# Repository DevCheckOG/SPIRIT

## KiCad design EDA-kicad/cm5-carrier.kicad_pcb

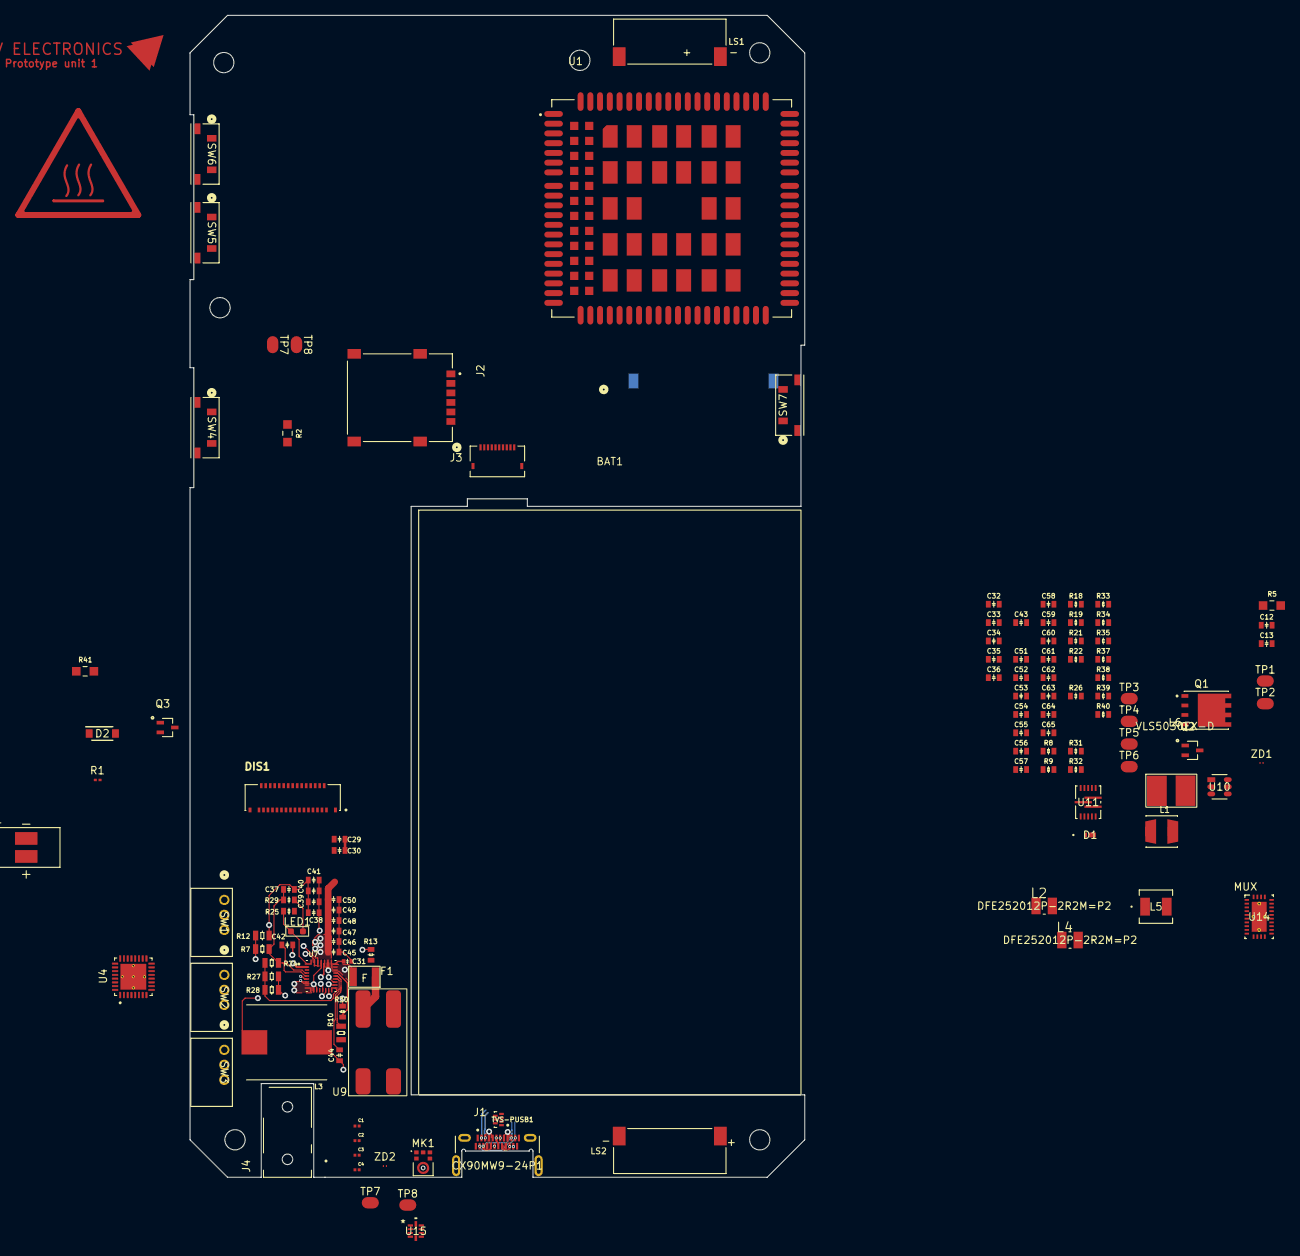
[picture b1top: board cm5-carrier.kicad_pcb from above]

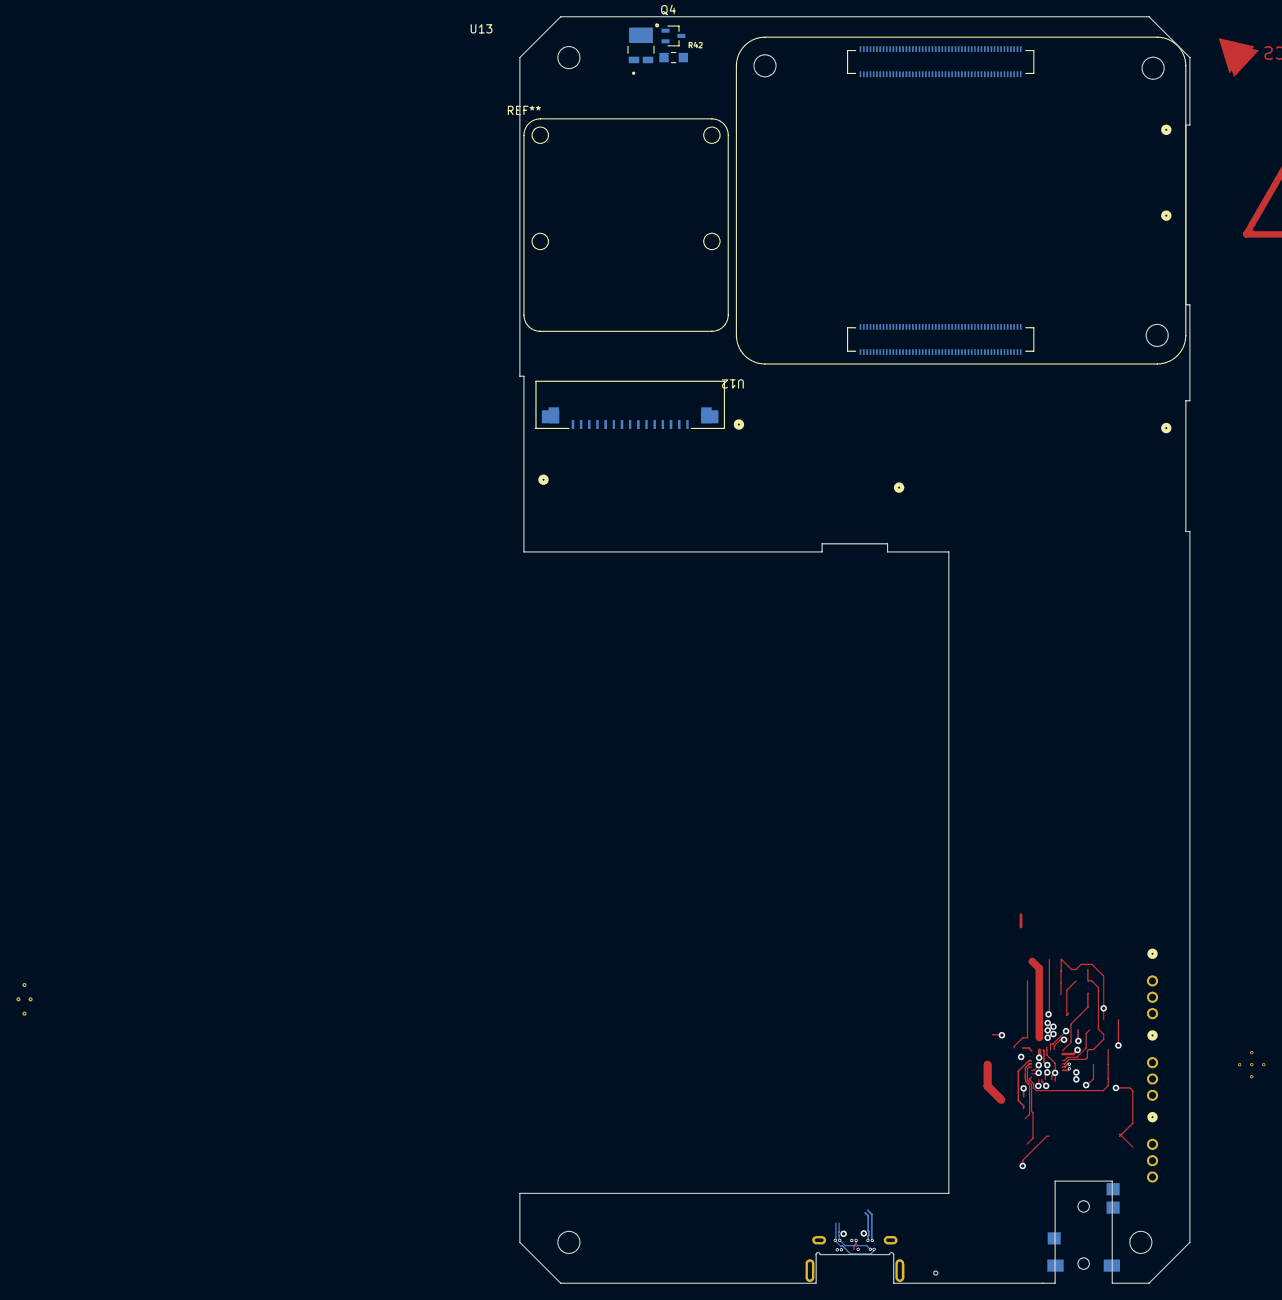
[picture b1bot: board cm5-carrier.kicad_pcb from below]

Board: 6 copper layers, 82.0 x 155.0 mm, 129 parts (5 on the bottom side), 101 nets.

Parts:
B1: VIBR; VIBRATION-PUI_HD-EMB1205-3-SC-R
BAT1: Li-ion-3.7 35Ah; battery_37V3500mAhLP685077JU
C1, C2, C3, C4: 0.33 µF coupling cap; USBC_capacitor_CAPC0603X33N
C12: 200pF; 0603-capacitor
C13, C38, C45, C55, C59: 0.1uF; 0603-capacitor
C29, C30, C33, C34, C35, C39, C40, C41, C46, C47, C48, C49, C50: 10uF; 0603-capacitor
C31: 1nF 50V; 0402-capacitor
C32, C53, C54: 1uF; 0603-capacitor
C36, C43, C51, C56, C57, C58, C60, C61, C62, C65: 22uF; 0603-capacitor
C37, C52, C64: 4.7uF; 0603-capacitor
C42, C44: 47nF; 0603-capacitor
C63: 6.8nF; 0603-capacitor
D1: D_Schottky; schottky-diode-CR_DSN2_152AB-C_OSI
D2: 1N4007W-T; flyback-diode-SODFL3818X130N
DIS1: FH72-31S-0.3SHW; HRS_FH72-31S-0.3SHW
F1: 9A 6V; PTC RESET FUSE 9.0A 6V 1210 1210L900SLPR
J1: USBC-4-0-CX90MW9-24P1; USB-4-0-HIROSE_CX90MW9-24P1
J2: SIM-G85D1160022HHR; SIM-AMPHENOL_G85D1160022HHR
J3: FINGER; 10PIN
J4: SJ2-35894B-SMT-TR; 35mmJACK-CUI_SJ2-35894B-SMT-TR
L1: 3.3uH; 3-3uH-MURATA_LQH44PN3R3MPRL
L2, L4: 2.2uH; 2-2uH-inductor-INDC2520X120N
L3: 2.2uH; 2-2uh-inductorIND_ETQP4M2R2KVC
L5: 6.8uH; 6-8uH-inductor-LQH44PN6R8MPRLIND_LQH44PN_PR_MUR
L6: 1.5uH; 1-5uH-inductor-VLS5030EX-D
LED1: 5mA 2V Fv; LED-INDICATOR-RED-QBLP601-R5
LS1, LS2: CMR-15062S-67; SPEAKER_CMR-15062S-67
MK1: microphone; microphone_SPH0645LM4H-B
Module1: ComputeModule5-CM5; Raspberry-Pi-5-Compute-Module
Q1: NMOS-BSC0902NSIATMA1-PG-TDSON-8-6-IC_ISC037N03L5ISATMA1
Q2, Q3, Q4: gpio-driver-transistor-fix-SOT65P210X110-3N
R1: thermistor; thermistor-NTC0201Z_P63XP33_PAN
R2: 270KΩ 0.5W; 1K-05W-0805-RES_ERJP06J102V
R5: 100KΩ; 100K-0805-resistor-RES_ERA6AEB104V
R7: 127kΩ; 0805-resistor
R8, R9: 10k; 0603-resistor
R10: 4.7KΩ; 0805-resistor
R12: 100kΩ; 0805-resistor
R13: 100Ω; 0603-resistor
R18, R31, R32, R33: 100kΩ; 0603-resistor
R19: 680kΩ 1%; 0603-resistor
R21, R26: 470kΩ 1%; 0603-resistor
R22: 1MΩ 1%; 0603-resistor
R24: 5.23kΩ; 0805-resistor
R25, R30: 10kΩ; 0603-resistor
R27: 10kΩ; 0805-resistor
R28: 30kΩ; 0805-resistor
R29: 680Ω; 0603-resistor
R34: 820kΩ; 0603-resistor
R35: 182KΩ; 0603-resistor
R37: 5Ω; 0603-resistor
R38: 750kΩ; 0603-resistor
R39: 200kΩ; 0603-resistor
R40: 6.8kΩ; 0603-resistor
R41, R42: 1KΩ 0.5W; 1K-05W-0805-RES_ERJP06J102V
SW1: EG25-switch-CSS-1210MC; privacy-switch-SW3_CSS-1210MC_NDC
SW2: MIC-switch-CSS-1210MC; privacy-switch-SW3_CSS-1210MC_NDC
SW3: CAM-switch-CSS-1210MC; privacy-switch-SW3_CSS-1210MC_NDC
SW4: PROG; buttonSW_TL3330_EWI
SW5: VOL-; buttonSW_TL3330_EWI
SW6: VOL+; buttonSW_TL3330_EWI
SW7: POW; buttonSW_TL3330_EWI
TP1, TP2, TP3, TP4, TP5, TP6, TP7, TP7#2, TP8, TP8#2: test-pad-1
TVS-PUSB1: TVS-array-IC_PUSB3AB6Z
U1: EG25GGC-128-SGNS; XCVR_EG25GGC-128-SGNS
U4: CODEC-TLV320AIC3204IRHBR; CODEC-QFN50P500X500X100-33N
U7: BQ25792RQMR; charger-bq25792-QFN40P400X400X100-29N
U9: BAT-CONNECTOR-FLTS22WR00
U10: 22V-boost-AP3032KTR-G1; SOT23-6_DIO
U11: MP3429GL-Z; QFN-3x4_MP3429_MNP
U12: FPC15pin-1mm-pitch-F52Q-1A7H1-11015; FPC15pin-1mm-pitch-CONN_F52Q-1A7H1-11015_AMP
U13: Flash-LED-Lumiled; LUMILED-DIODFN449X305X210-3N
U14: HD3SS460RHRR; USB-MUX-RHR0028A
U15: USB SWITCH 2CHANNEL TS3USB221AQRSERQ1; USB-SWITCH-2CHANNEL-TS3USB221AQRSERQ1
ZD1, ZD2: protection-PESD5V0C1USFYL; USB-ESD-protection-diode-PESD5V0C1USFYL-SOD962-2_DSN0603-2_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

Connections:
1V8: DIS1.25, SW2.1, U4.24 (AVDD), U4.29 (DVDD)
3V3B: DIS1.30, Module1.78 (GPIO_VREF(1.8v/3.3v_Input)), Q2.3 (S), R8.2, R9.1, R25.2, R30.1, R31.1, R32.1, R33.2, SW3.1, U4.6 (IOVDD), U4.26 (LDOIN/HPVDD), U4.30 (LDO_SELECT)
5V: C59.1, C60.1, C61.1, C62.1, Module1.77 (+5v_(Input)), Module1.79 (+5v_(Input)), Module1.81 (+5v_(Input)), Module1.83 (+5v_(Input)), Module1.85 (+5v_(Input)), Module1.87 (+5v_(Input)), R38.1, U11.8 (VOUT)
22V: C53.1, D1.1 (K), DIS1.2, U10.5 (OV)
AGND: C65.2, R39.2, R40.2, U11.6 (AGND), U11.9 (FTY)
AUDIO_BCLK_I2S: MK1.4 (BCLK), Module1.49 (GPIO18), U4.2 (BCLK)
AUDIO_MCLK: Module1.54 (GPIO4), U4.1 (MCLK)
AUDIO_MIC_DATA: Module1.27 (GPIO20), U4.5 (DOUT/MFP2)
AUDIO_RESET: Module1.45 (GPIO24), U4.31 (~RESET)
AUDIO_SCL: Module1.51 (GPIO15), U4.9 (SCL/~SS)
AUDIO_SDA: Module1.31 (GPIO12), U4.10 (SDA/MOSI)
AUDIO_SOUND_DATA: Module1.25 (GPIO21), U4.4 (DIN/MFP1)
AUDIO_WCLK_I2S: MK1.1 (WS), Module1.26 (GPIO19), U4.3 (WCLK)
BACKLIGHT-: DIS1.31, R37.1, U10.3 (FB)
BAT+: C29.1, C30.1, F1.2, R13.2, U7.22 (BAT), U7.23 (BAT__1)
CAM-SWITCH: TP7.1 (A), U12.15
CAM_CK_N: Module1.127 (MIPI0_C_N), U12.8
CAM_CK_P: Module1.129 (MIPI0_C_P), U12.9
CAM_D0_N: Module1.115 (MIPI0_D0_N), U12.2
CAM_D0_P: Module1.117 (MIPI0_D0_P), U12.3
CAM_D1_N: Module1.121 (MIPI0_D1_N), U12.5
CAM_D1_P: Module1.123 (MIPI0_D1_P), U12.6
CAM_IO0: TP8.1 (A), U12.11
CC1: J1.A5 (CC1), Module1.94 (CC1)
CC2: J1.B5 (CC2), Module1.96 (CC2)
D+: J1.A6 (D1+), J1.B6 (D2+), Module1.163 (USB3-1-D_P), TVS-PUSB1.5 (D+), U7.6 (D+)
D-: J1.A7 (D1-), J1.B7 (D2-), Module1.165 (USB3-1-D_N), TVS-PUSB1.4 (D-), U7.7 (D-)
DEFDCDC1 DIVIDER: C36.1, L1.1, R34.1
DSI1_C_N: DIS1.11, Module1.187 (MIPI1_C_N)
DSI1_C_P: DIS1.12, Module1.189 (MIPI1_C_P)
DSI1_D0_N: DIS1.5, Module1.175 (MIPI1_D0_N)
DSI1_D0_P: DIS1.6, Module1.177 (MIPI1_D0_P)
DSI1_D1_N: DIS1.8, Module1.181 (MIPI1_D1_N)
DSI1_D1_P: DIS1.9, Module1.183 (MIPI1_D1_P)
DSI1_D2_N: DIS1.14, Module1.133 (MIPI0_D2_N), Module1.193 (MIPI1_D2_N)
DSI1_D2_P: DIS1.15, Module1.135 (MIPI0_D2_P), Module1.195 (MIPI1_D2_P)
GND: C12.1, C13.2, C29.2, C30.2, C31.2, C32.2, C33.2, C34.2, C35.2, C36.2, C37.2, C38.2, C39.2, C40.2, C41.2, C43.2, C45.2, C46.2, C47.2, C48.2, C49.2, C50.2, C51.2, C52.1, C53.2, C54.2, C56.2, C57.2, C58.2, C59.2, C60.2, C61.2, C62.2, C64.1, DIS1.1, DIS1.4, DIS1.7, DIS1.10, DIS1.13, DIS1.16, DIS1.19, DIS1.20, J1.A1 (GND_A), J1.A12 (GND_A__1), J1.B1 (GND_B), J1.B12 (GND_B__1), J1.SH1 (SHIELD), J1.SH2 (SHIELD__1), J1.SH3 (SHIELD__2), J1.SH4 (SHIELD__3), J2.C5 (GND), J2.S1 (SHIELD_GND), J2.S2 (SHIELD_GND__1), J2.S3 (SHIELD_GND__2), J3.1, J4.1, MK1.2 (SELECT), MK1.3 (GND), Module1.1 (GND), Module1.2 (GND), Module1.8 (GND), Module1.13 (GND), Module1.14 (GND), Module1.22 (GND), Module1.23 (GND), Module1.32 (GND), Module1.33 (GND), Module1.42 (GND), Module1.43 (GND), Module1.52 (GND), Module1.53 (GND), Module1.60 (GND), Module1.66 (GND), Module1.71 (GND), Module1.74 (GND), Module1.98 (GND), Module1.107 (GND), Module1.108 (GND), Module1.113 (GND), Module1.114 (GND), Module1.119 (GND), Module1.120 (GND), Module1.125 (GND), Module1.126 (GND), Module1.131 (GND), Module1.132 (GND), Module1.137 (GND), Module1.138 (GND), Module1.144 (GND), Module1.150 (GND), Module1.155 (GND), Module1.156 (GND), Module1.161 (GND), Module1.162 (GND), Module1.167 (GND), Module1.168 (GND), Module1.173 (GND), Module1.174 (GND), Module1.179 (GND), Module1.180 (GND), Module1.185 (GND), Module1.186 (GND), Module1.191 (GND), Module1.192 (GND), Module1.197 (GND), Module1.198 (GND), Q3.3 (S), Q4.3 (S), R5.1, R10.1, R12.2, R21.1, R26.1, R27.2, R28.2, R35.1, R37.2, TVS-PUSB1.2 (GND), U4.7 (IOVSS), U4.12 (SPI_SELECT), U4.17 (AVSS), U4.28 (DVSS), U4.33 (EP), U7.10 (ACDRV2), U7.11 (ACDRV1), U7.27 (GND), U9.4 (OUT-), U10.2 (GND), U11.7 (PGND), U12.1, U12.4, U12.10, ZD1.2, ZD2.2
GPIO2: Module1.58 (GPIO2), SW7.2
GPIO3: Module1.56 (GPIO3), SW6.2
GPIO17: Module1.50 (GPIO17), SW4.2
GPIO22: Module1.46 (GPIO22), R42.1
GPIO27: Module1.48 (GPIO27), R41.1
JACK_MIC: J4.4, U4.8 (SCLK/MFP3)
LCD_PWM: Module1.55 (GPIO14), U10.4 (CTRL)
MIC-SWITCH: C12.2, C13.1, MK1.5 (VDD)
unnamed: C63.2, R40.1
unnamed: D1.2 (A), L5.2, U10.1 (SW)
unnamed: J3.8, R2.2
unnamed: LED1.2 (A), R29.1
unnamed: LED1.1 (K), R25.1, U7.1 (STAT)
unnamed: MK1.6 (DATA_OUT), R5.2
unnamed: C1.1, Module1.157 (USB3-1-RX_N)
unnamed: C2.1, Module1.159 (USB3-1-RX_P)
unnamed: C3.1, Module1.169 (USB3-1-TX_N)
unnamed: C4.1, Module1.171 (USB3-1-TX_P)
unnamed: Q2.1 (G), SW3.2
unnamed: B1.N, D2.2, Q3.2 (D)
unnamed: Q3.1 (G), R41.2
unnamed: Q4.2 (D), U13.1 (-)
unnamed: Q4.1 (G), R42.2
unnamed: C52.2, TP5.1 (A)
unnamed: R13.1, U7.18 (BATP)
unnamed: C42.2, U7.4 (BTST1)
unnamed: C44.2, U7.19 (BTST2)
unnamed: R7.1, R12.1, U7.17 (ILIM_HIZ)
unnamed: C38.1, C39.1, C40.1, C41.1, U7.29 (PMID)
unnamed: R10.2, U7.20 (PROG)
unnamed: C31.1, U7.24 (SDRV)
unnamed: C42.1, L3.2, U7.28 (SW1)
unnamed: C44.1, L3.1, U7.26 (SW2)
unnamed: R24.2, R27.1, R28.1, U7.16 (TS)
unnamed: R34.2, R35.2
unnamed: R22.1, R26.2
unnamed: R19.1, R21.2
unnamed: C32.1, R18.1
unnamed: C43.1, L2.1
unnamed: C51.1, L4.1
unnamed: F1.1, U9.3 (OUT+)
unnamed: C55.1, U11.13 (BST)
unnamed: C63.1, U11.4 (COMP)
unnamed: R38.2, R39.1, U11.5 (FB)
unnamed: C65.1, U11.3 (SS)
unnamed: C55.2, L6.2, U11.1 (SW)
unnamed: C64.2, U11.2 (VDD)
REGN: C37.1, R7.2, R24.1, R29.2, U7.5 (REGN)
RX1+: C2.2, J1.A11 (RX2+), J1.B11 (RX1+), TVS-PUSB1.7 (RX+)
RX1-: C1.2, J1.A10 (RX2-), J1.B10 (RX1-), TVS-PUSB1.6 (Rx-)
SCL PWR: Module1.80 (SCL0), U7.14 (SCL)
SDA PWR: Module1.82 (SDA0), U7.15 (SDA)
SPI0_CLK: J3.2, Module1.38 (GPIO11)
SPI0_CS: J3.5, Module1.39 (GPIO8)
SPI0_MISO: J3.3, Module1.40 (GPIO9)
SPI0_MOSI: J3.4, Module1.44 (GPIO10)
SPI0_RDY: J3.6, Module1.34 (GPIO5)
SYS: C45.1, C46.1, C47.1, C48.1, C49.1, C50.1, C54.1, C56.1, C57.1, C58.1, L5.1, L6.1, R19.2, R22.2, U7.25 (SYS), U10.6 (VIN), U11.10 (MODE), U11.11 (EN), U11.12 (VIN)
TX1+: C4.2, J1.A2 (TX1+), J1.B2 (TX2+), TVS-PUSB1.3 (Tx+)
TX1-: C3.2, J1.A3 (TX1-), J1.B3 (TX2-), TVS-PUSB1.1 (Tx-)
USBC POW: J1.A4 (VBUS_A), J1.A9 (VBUS_A__1), J1.B4 (VBUS_B), J1.B9 (VBUS_B__1), U7.2 (VBUS), U7.8 (VAC2), U7.9 (VAC1), ZD1.1, ZD2.1
VCC: B1.P, D2.1, J3.7, J3.10, R2.1, SW4.1, SW5.1, SW6.1, SW7.1, U13.2 (+)
~BQ INT: R30.2, U7.21 (~INT)
~TPS INT: R31.2, TP6.1 (A)

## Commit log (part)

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2026-03-19 fix bad label 3V3
2026-03-19 pull up I2C line of TPS
2026-03-19 Fixed audio schematic file name
2026-03-19 Finished audio schematic
2026-03-22 change netflaf for microphone switch to be 1V8 instead of 3V3B, GPS/GSM symbol
2026-03-22 reannotate entire schematic
2026-03-22 broken connection, change flags to 3V3B labels
2026-03-22 screen GND ref
2026-03-22 charger 50% routed
2026-03-23 update schematic PDF
2026-03-24 connect GPIO VREF to 3V3B
2026-03-24 remove redundant pull ups, connect charger and PMIC on single I2C bus
2026-03-24 routed charger
2026-03-24 add MPN to USB C symbol
2026-03-24 fix USB C cutout
2026-04-25 improve DNP automation, exclude root and USB
2026-04-25 add USB-MUX HD3SS460
2026-04-25 add USB 2 switch
2026-04-25 connect USB switch
2026-04-25 change some labels
2026-04-25 connect charger to usb switch
2026-04-25 initial MUX connections
2026-04-28 add image of selected MUX config
